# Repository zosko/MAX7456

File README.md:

# MAX7456
OSD Module board for MAX7456 / AT7456

Datasheet: MAX7456 - https://www.analog.com/media/en/technical-documentation/data-sheets/MAX7456.pdf

This is a breakout board for the Maxim MAX7456 monochrome on-screen display chip. The board is set up with all supporting circuitry and RCA connectors to allow the user to easily interrupt and overlay text and/or graphics onto a video signal (PAL or NTSC).

## Scheme XIAO

## KiCad XIAO
Board|PCB
----|----
|

## Scheme

Board|PCB
----|----
|

## Code

There are several libraries for this project to work. 
Library: https://github.com/neomilium/arduino-max7456/

First you need to upload charset into MAX7456 in order to use it.

```c
#include <SPI.h>
#include <max7456.h>

Max7456       osd;

void setup() {
  SPI.begin();

  osd.init(10);
  osd.setDisplayOffsets(60, 18);
  osd.setBlinkParams(_8fields, _BT_BT);
  osd.activateOSD();
  osd.print("Hello world :)", 1, 3);
}
void loop() { }
```

## PCB Design

For PCB design i will use services from SeeedFusion. 

Seeed Fusion PCB Assembly Service offers one-stop prototyping for PCB manufacture, PCB assembly and as a result they produce superior quality PCBs and Fast Turnkey PCBA from 7 working days. When you prototype with Seeed Fusion, they can definitely provide Free DFA and Free functional tests for you! 

Check out their website to know about their manufacturing capabilities and service.
https://www.seeedstudio.com/pcb-assembly.html

Seeed Fusion Agile manufacturing: https://seeedstudio.com/fusion.htm

## Reasons to choose Seeed Studio
- They provide PCB services at extremely low pricing and with excellent quality.
- Their offer is structured in such a way that everyone may have these boards at a reasonable price.
- They have a highly knowledgeable crew that leads their clients to avail deals and guides them about the costs and rates of different services.
- A four-layer board with a comparable feature costs $5 for 10 pieces and is made in four days.
- SMT stencil with size (10cm x 13cm) is available for $8.00 per piece.

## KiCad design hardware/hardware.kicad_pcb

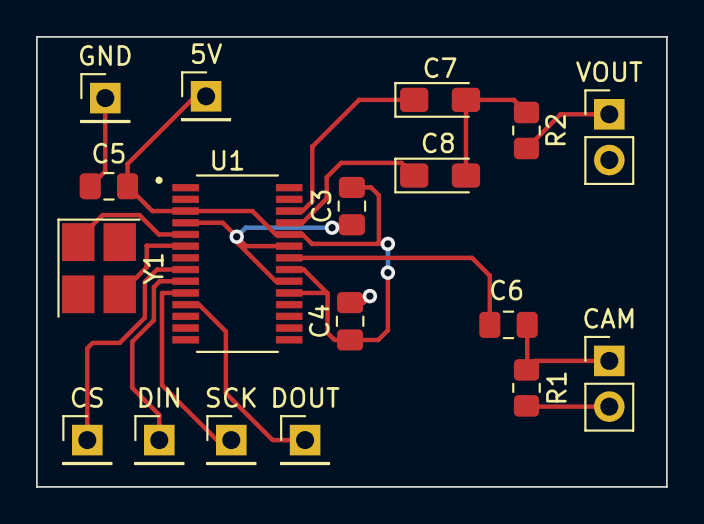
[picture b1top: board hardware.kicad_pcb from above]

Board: 2 copper layers, 35.0 x 25.0 mm, 18 parts (0 on the bottom side), 14 nets.

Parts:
5V: 5V; PinHeader_1x01_P2.54mm_Vertical
C3, C4, C5, C6: 100nF; C_0805_2012Metric_Pad1.18x1.45mm_HandSolder
C7, C8: 47uF; CP_EIA-3216-18_Kemet-A_Pad1.58x1.35mm_HandSolder
CAM: VIN; PinHeader_1x02_P2.54mm_Vertical
CS: CS; PinHeader_1x01_P2.54mm_Vertical
DIN: DIN; PinHeader_1x01_P2.54mm_Vertical
DOUT: DOUT; PinHeader_1x01_P2.54mm_Vertical
GND: GND; PinHeader_1x01_P2.54mm_Vertical
R1, R2: 75; R_0805_2012Metric_Pad1.20x1.40mm_HandSolder
SCK: SCK; PinHeader_1x01_P2.54mm_Vertical
U1: MAX7456EUI+; SOP65P637X110-28N
VOUT: VOUT; PinHeader_1x02_P2.54mm_Vertical
Y1: 27MHZ; Crystal_SMD_3225-4Pin_3.2x2.5mm_HandSoldering

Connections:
5V: 5V.1, C3.2, C4.1, C5.1, U1.3 (DVDD), U1.19 (~RESET), U1.21 (AVDD), U1.24 (PVDD)
CS: CS.1, U1.8 (~CS)
DIN: DIN.1, U1.9 (SDIN)
DOUT: DOUT.1, U1.11 (SDOUT)
GND: C3.1, C4.2, C5.2, CAM.2, GND.1, R1.1, U1.4 (DGND), U1.20 (AGND), U1.23 (PGND), VOUT.2
unnamed: C7.2, C8.2, R2.1
unnamed: C6.2, CAM.1, R1.2
unnamed: R2.2, VOUT.1
SAG: C8.1, U1.25 (SAG)
SCK: SCK.1, U1.10 (SCLK)
VIN: C6.1, U1.22 (VIN)
VOUT: C7.1, U1.26 (VOUT)
XTAL1: U1.5 (CLKIN), Y1.1
XTAL2: U1.6 (XFB), Y1.3

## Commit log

2022-12-21 add images
2022-12-21 add project
2023-06-26 redesign
2023-06-30 xiao board
2023-06-30 add xiao project
2023-08-19 fix lines
